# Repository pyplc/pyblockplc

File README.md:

# Python PLC Automation FBD- Programming with ESP32 Micropython

Pyblockplc is FBD programming for PLC, as PLC is here to be more precise an ESP32 uses Lolin D32 Pro.
Basis Micropython and as a PLC operating system a Python program called The ESP32 runs as
plc_os_v1_0.mpy, the program plc_os_v1_0.mpy is the main program in Mircopython is called in main.py in ESP32.
Pyblockplc IDE compiles a file called program.json, the file program.json must be loaded into the root directory of the ESP32 and restarted by restart or start the board.

pyblockplc FBD- Editor

pyblockplc Simulator

plc prototype hardware 24V, 6 input, 4 relais output.

Din rail case - APRA HO6

License:

PC program  pyblockplc _v1_0.exe - Freeware

Plc program plc_os_v1_0.mpy - Freeware

Hardware Kicad project - Licensed under CERN OHL v.1.2

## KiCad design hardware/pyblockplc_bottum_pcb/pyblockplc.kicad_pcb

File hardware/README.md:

# Prototyp PCB plc

Created with  KiCad 5.1.10

Licensed under CERN OHL v.1.2

PCB bottom:

PCB midle:

PCB top:

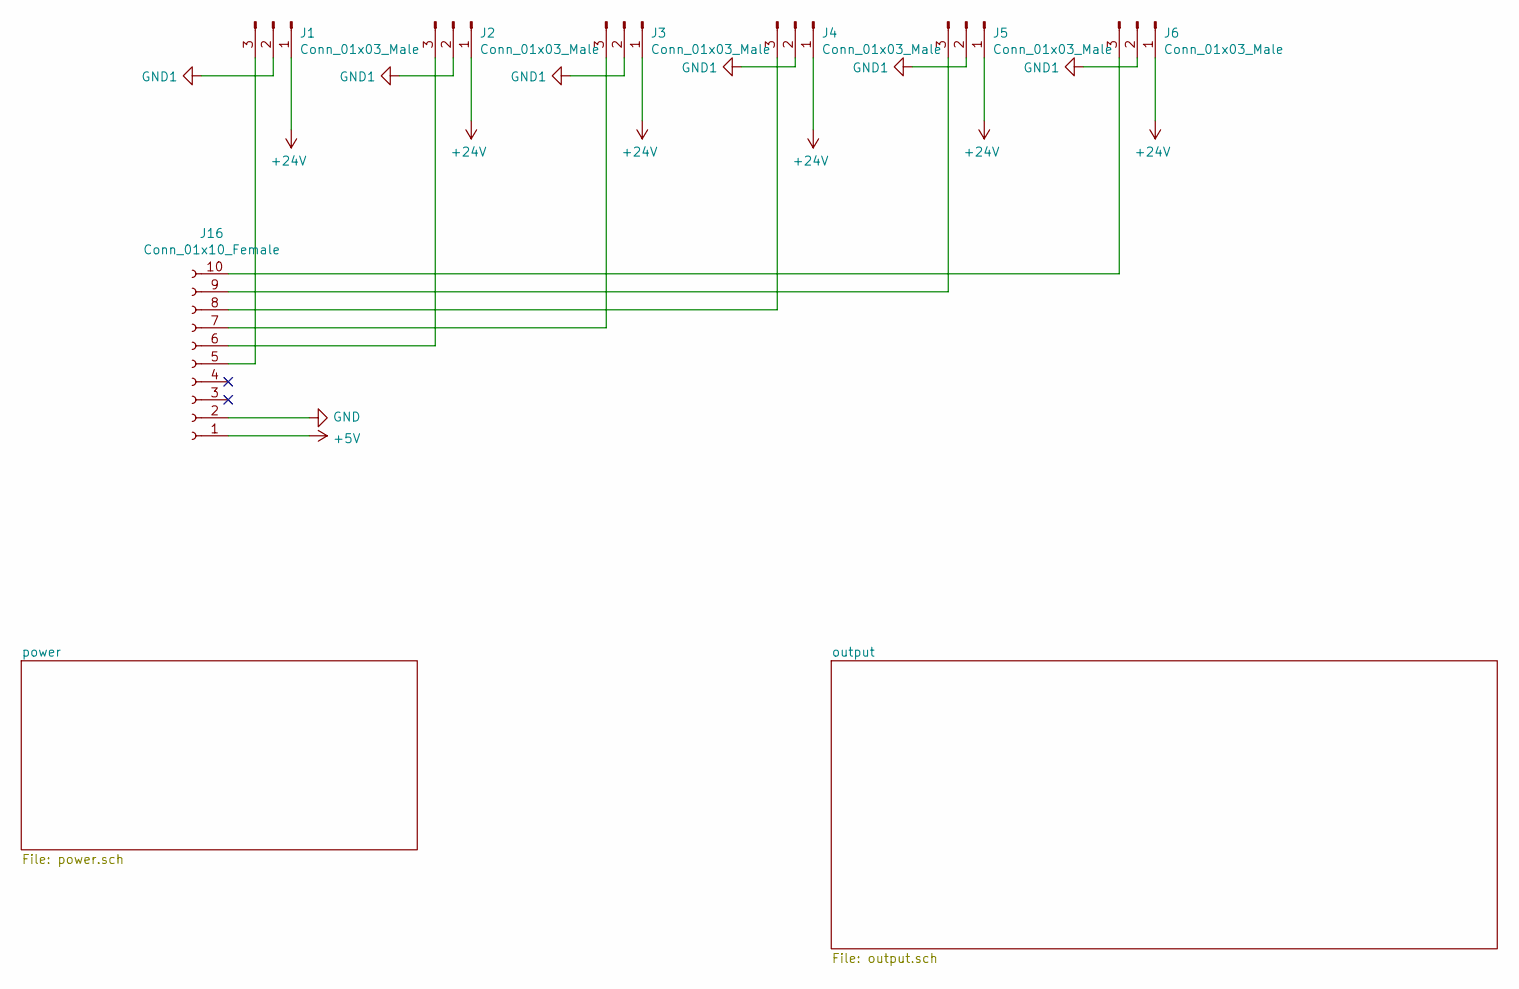
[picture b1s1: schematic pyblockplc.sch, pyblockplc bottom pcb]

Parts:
J1, J2, J3, J4, J5, J6: Conn_01x03_Male; JST_NV_B03P-NV_1x03_P5.00mm_Vertical
J16: Conn_01x10_Female; PinSocket_1x10_P2.54mm_Vertical

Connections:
+5V: J16.1; also elsewhere on the board
+24V: J1.1, J2.1, J3.1, J4.1, J5.1, J6.1; also elsewhere on the board
GND: J16.2; also elsewhere on the board
GND1: J1.2, J2.2, J3.2, J4.2, J5.2, J6.2; also elsewhere on the board
unnamed: J1.3, J16.5
unnamed: J2.3, J16.6
unnamed: J3.3, J16.7
unnamed: J4.3, J16.8
unnamed: J5.3, J16.9
unnamed: J6.3, J16.10

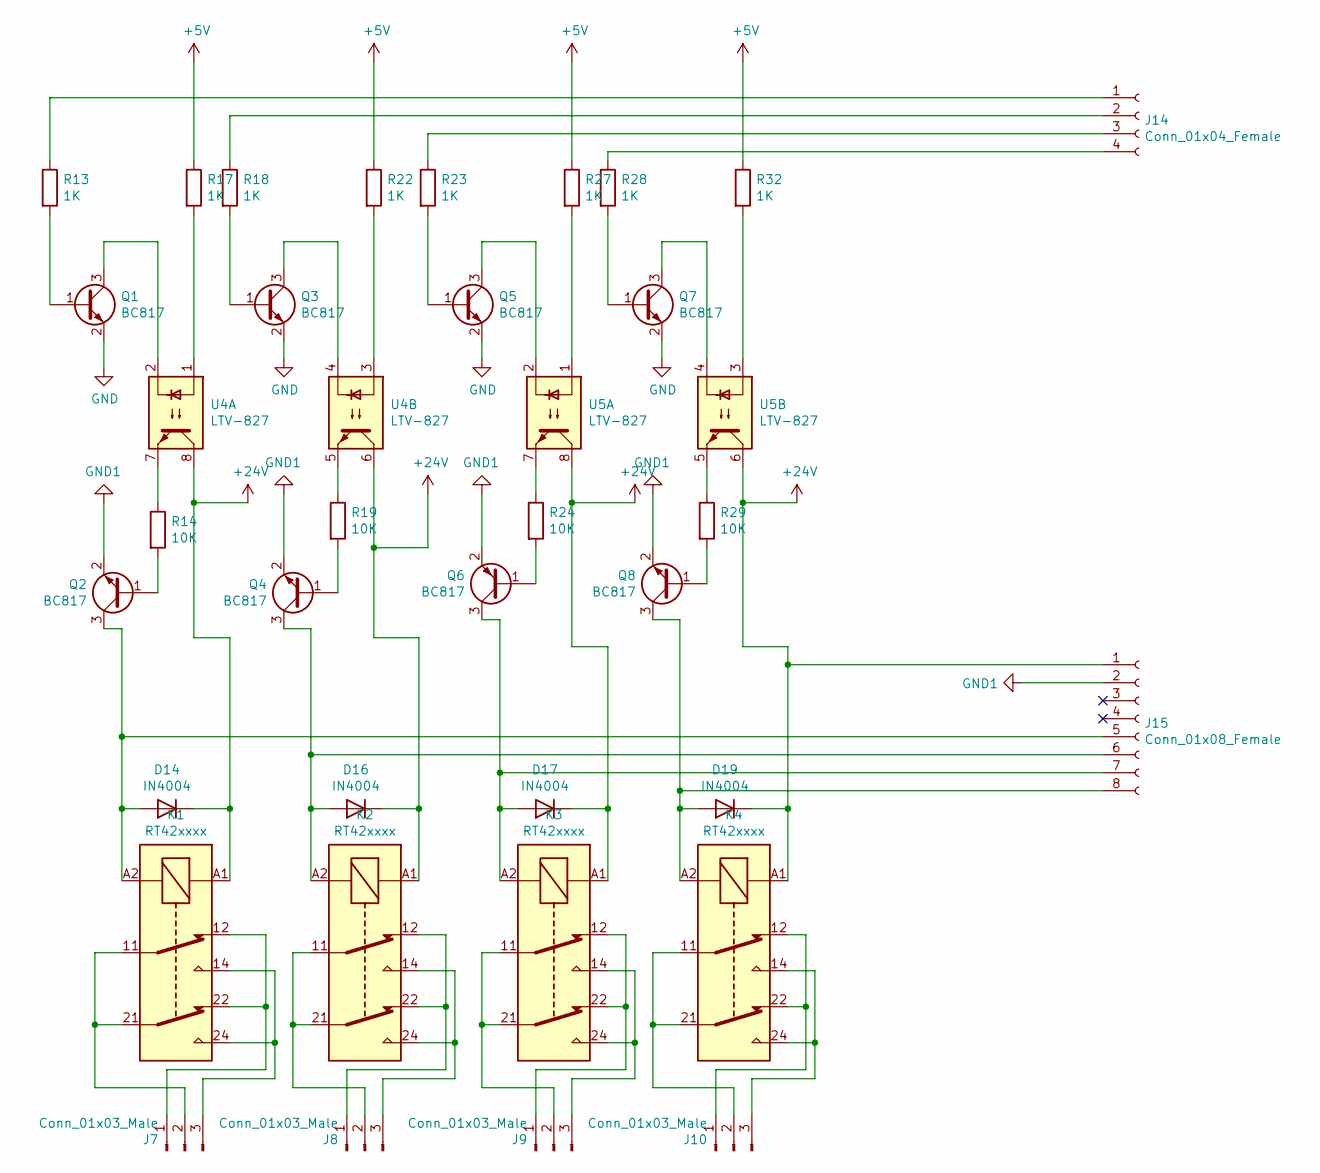
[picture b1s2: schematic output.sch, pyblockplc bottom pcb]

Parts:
D14, D16, D17, D19: IN4004; D_SMA
J7, J8, J9, J10: Conn_01x03_Male; JST_NV_B03P-NV_1x03_P5.00mm_Vertical
J14: Conn_01x04_Female; PinSocket_1x04_P2.54mm_Vertical
J15: Conn_01x08_Female; PinSocket_1x08_P2.54mm_Vertical
K1, K2, K3, K4: RT42xxxx; Relay_SPDT_Schrack-RP-II-1-16A-FormC_RM5mm
Q1, Q2, Q3, Q4, Q5, Q6, Q7, Q8: BC817; SOT-23
R13, R17, R18, R22, R23, R27, R28, R32: 1K; R_1206_3216Metric
R14, R19, R24, R29: 10K; R_1206_3216Metric
U4, U5: LTV-827; DIP-8_W8.89mm_SMDSocket_LongPads

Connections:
+5V: R17.1, R22.1, R27.1, R32.1; also elsewhere on the board
+24V: D14.1 (K), D16.1 (K), D17.1 (K), D19.1 (K), J15.1, K1.A1, K2.A1, K3.A1, K4.A1, U4.6, U4.8, U5.6, U5.8; also elsewhere on the board
GND: Q1.2 (E), Q3.2 (E), Q5.2 (E), Q7.2 (E); also elsewhere on the board
GND1: J15.2, Q2.2 (E), Q4.2 (E), Q6.2 (E), Q8.2 (E); also elsewhere on the board
unnamed: D14.2 (A), J15.5, K1.A2, Q2.3 (C)
unnamed: D16.2 (A), J15.6, K2.A2, Q4.3 (C)
unnamed: D17.2 (A), J15.7, K3.A2, Q6.3 (C)
unnamed: D19.2 (A), J15.8, K4.A2, Q8.3 (C)
unnamed: J7.1, K1.12, K1.22
unnamed: J7.2, K1.11, K1.21
unnamed: J7.3, K1.14, K1.24
unnamed: J8.1, K2.12, K2.22
unnamed: J8.2, K2.11, K2.21
unnamed: J8.3, K2.14, K2.24
unnamed: J9.1, K3.12, K3.22
unnamed: J9.2, K3.11, K3.21
unnamed: J9.3, K3.14, K3.24
unnamed: J10.1, K4.12, K4.22
unnamed: J10.2, K4.11, K4.21
unnamed: J10.3, K4.14, K4.24
unnamed: J14.1, R13.1
unnamed: J14.2, R18.1
unnamed: J14.3, R23.1
unnamed: J14.4, R28.1
unnamed: Q1.1 (B), R13.2
unnamed: Q1.3 (C), U4.2
unnamed: Q2.1 (B), R14.2
unnamed: Q3.1 (B), R18.2
unnamed: Q3.3 (C), U4.4
unnamed: Q4.1 (B), R19.2
unnamed: Q5.1 (B), R23.2
unnamed: Q5.3 (C), U5.2
unnamed: Q6.1 (B), R24.2
unnamed: Q7.1 (B), R28.2
unnamed: Q7.3 (C), U5.4
unnamed: Q8.1 (B), R29.2
unnamed: R14.1, U4.7
unnamed: R17.2, U4.1
unnamed: R19.1, U4.5
unnamed: R22.2, U4.3
unnamed: R24.1, U5.7
unnamed: R27.2, U5.1
unnamed: R29.1, U5.5
unnamed: R32.2, U5.3

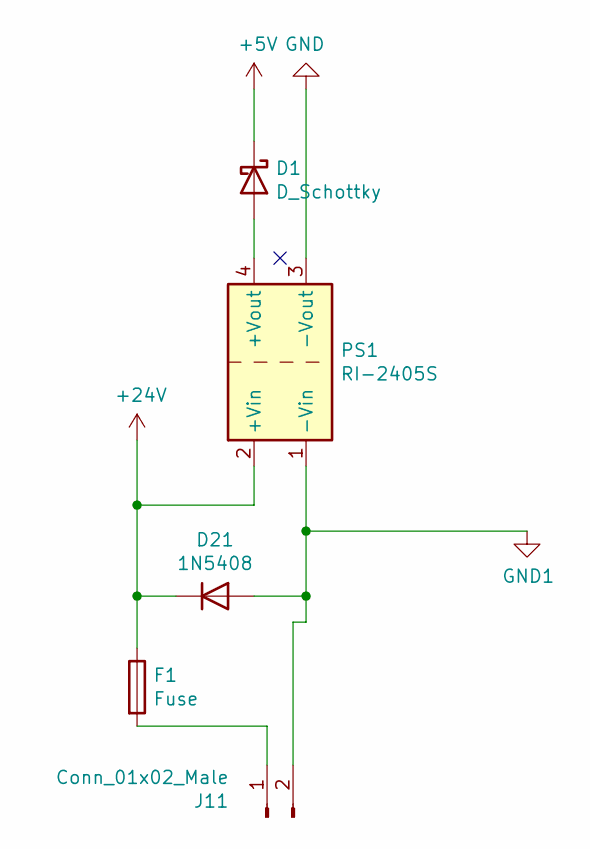
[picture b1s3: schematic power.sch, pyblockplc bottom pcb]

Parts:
D1: D_Schottky; D_SMA
D21: 1N5408; D_DO-201AD_P15.24mm_Horizontal
F1: Fuse; Fuseholder_Cylinder-5x20mm_Schurter_0031_8201_Horizontal_Op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
J11: Conn_01x02_Male; JST_NV_B02P-NV_1x02_P5.00mm_Vertical
PS1: RI-2405S; Converter_DCDC_RECOM_R-78S-0.1_THT

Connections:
+5V: D1.1 (K); also elsewhere on the board
+24V: D21.1 (K), F1.1, PS1.2 (+Vin); also elsewhere on the board
GND: PS1.3 (-Vout); also elsewhere on the board
GND1: D21.2 (A), J11.2, PS1.1 (-Vin); also elsewhere on the board
unnamed: D1.2 (A), PS1.4 (+Vout)
unnamed: F1.2, J11.1

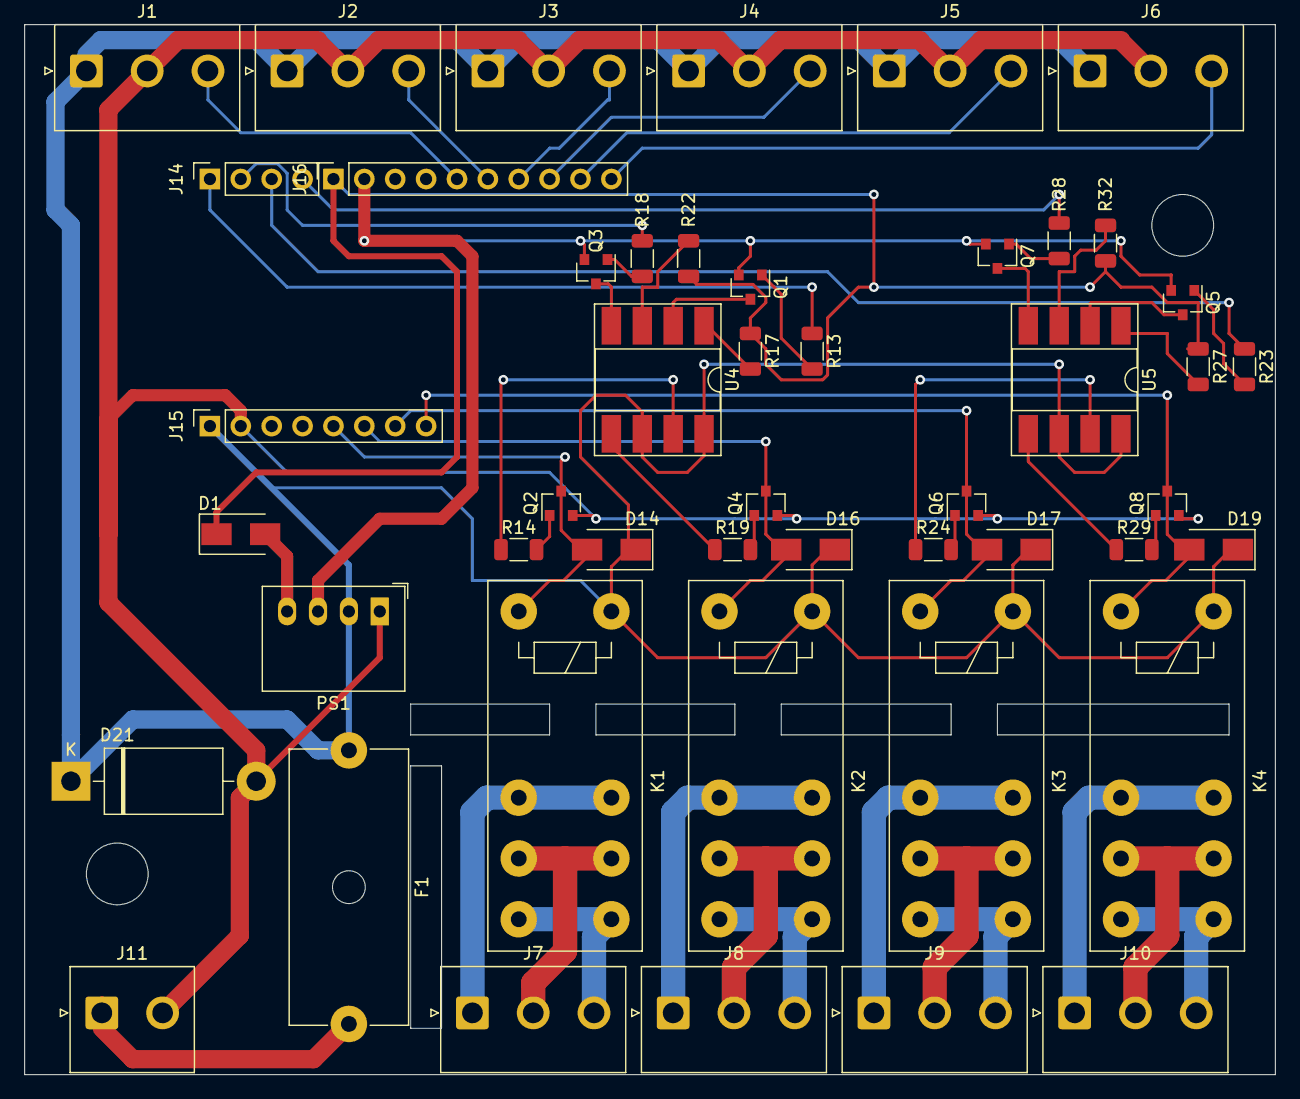
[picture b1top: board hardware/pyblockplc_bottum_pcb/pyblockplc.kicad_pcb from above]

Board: 2 copper layers, 102.9 x 86.4 mm, 48 parts (0 on the bottom side), 52 nets.

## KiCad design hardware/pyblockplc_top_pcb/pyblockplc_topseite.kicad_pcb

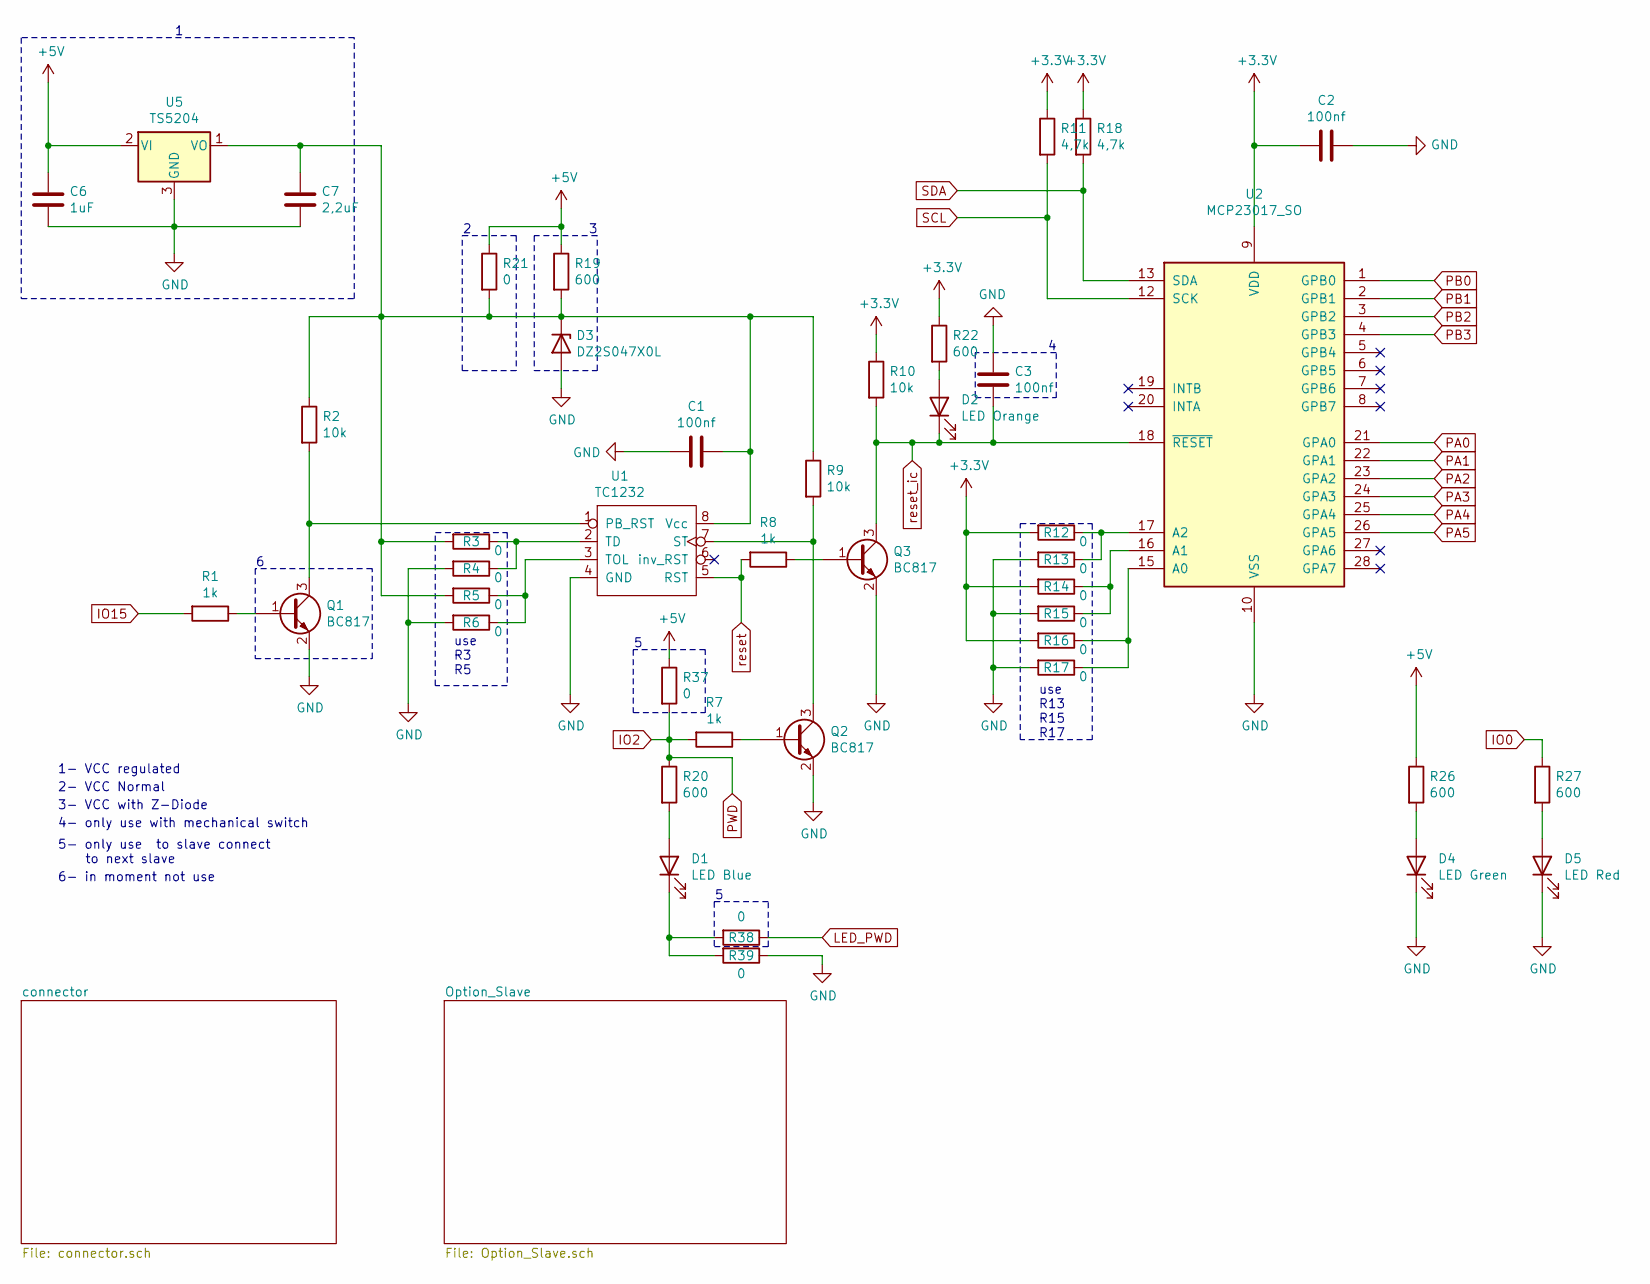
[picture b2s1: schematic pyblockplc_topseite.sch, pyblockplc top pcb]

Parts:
C1, C2, C3: 100nf; C_1206_3216Metric
C6: 1uF; CP_Elec_4x5.8
C7: 2,2uF; CP_Elec_4x5.8
D1: LED Blue; LED_1206_3216Metric_Castellated
D2: LED Orange; LED_1206_3216Metric_Castellated
D3: DZ2S047X0L; D_1206_3216Metric
D4: LED Green; LED_1206_3216Metric_Castellated
D5: LED Red; LED_1206_3216Metric_Castellated
Q1, Q2, Q3: BC817; SOT-23
R1, R7, R8: 1k; R_1206_3216Metric
R2, R9, R10: 10k; R_1206_3216Metric
R3, R4, R5, R6, R12, R13, R14, R15, R16, R17, R21, R37, R38, R39: 0; R_1206_3216Metric
R11, R18: 4,7k; R_1206_3216Metric
R19, R20, R22, R26, R27: 600; R_1206_3216Metric
U1: TC1232; SOIC-8_3.9x4.9mm_P1.27mm
U2: MCP23017_SO; SOIC-28W_7.5x17.9mm_P1.27mm
U5: TS5204; SOT-23

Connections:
+3V3: C2.2, R10.1, R11.1, R12.2, R14.2, R16.2, R18.1, R22.1, U2.9 (VDD); also elsewhere on the board
+5V: C6.1, R19.1, R21.1, R26.1, R37.1, U5.2 (VI); also elsewhere on the board
GND: C1.2, C2.1, C3.1, C6.2, C7.2, D3.2 (A), D4.1 (K), D5.1 (K), Q1.2 (E), Q2.2 (E), Q3.2 (E), R4.2, R6.2, R13.2, R15.2, R17.2, R39.1, U1.4 (GND), U2.10 (VSS), U5.3 (GND); also elsewhere on the board
IO0: R27.1; also elsewhere on the board
IO2: R7.2, R20.1, R37.2; also elsewhere on the board
IO15: R1.2; also elsewhere on the board
LED_PWD: R38.1; also elsewhere on the board
unnamed: C1.1, C7.1, D3.1 (K), R2.1, R3.2, R5.2, R9.1, R19.2, R21.2, U1.8 (Vcc), U5.1 (VO)
unnamed: D1.1 (K), R38.2, R39.2
unnamed: D1.2 (A), R20.2
unnamed: D2.2 (A), R22.2
unnamed: D4.2 (A), R26.2
unnamed: D5.2 (A), R27.2
unnamed: Q1.1 (B), R1.1
unnamed: Q1.3 (C), R2.2, U1.1 (PB_RST)
unnamed: Q2.1 (B), R7.1
unnamed: Q2.3 (C), R9.2, U1.7 (ST)
unnamed: Q3.1 (B), R8.1
unnamed: R3.1, R4.1, U1.2 (TD)
unnamed: R5.1, R6.1, U1.3 (TOL)
unnamed: R12.1, R13.1, U2.17 (A2)
unnamed: R14.1, R15.1, U2.16 (A1)
unnamed: R16.1, R17.1, U2.15 (A0)
PA0: U2.21 (GPA0); also elsewhere on the board
PA1: U2.22 (GPA1); also elsewhere on the board
PA2: U2.23 (GPA2); also elsewhere on the board
PA3: U2.24 (GPA3); also elsewhere on the board
PA4: U2.25 (GPA4); also elsewhere on the board
PA5: U2.26 (GPA5); also elsewhere on the board
PB0: U2.1 (GPB0); also elsewhere on the board
PB1: U2.2 (GPB1); also elsewhere on the board
PB2: U2.3 (GPB2); also elsewhere on the board
PB3: U2.4 (GPB3); also elsewhere on the board
SCL: R11.2, U2.12 (SCK); also elsewhere on the board
SDA: R18.2, U2.13 (SDA); also elsewhere on the board
reset: R8.2, U1.5 (RST); also elsewhere on the board
reset_ic: C3.2, D2.1 (K), Q3.3 (C), R10.2, U2.18 (~RESET~); also elsewhere on the board

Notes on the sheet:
2- VCC Normal
3- VCC with Z-Diode
1- VCC regulated
4- only use with mechanical switch
5- only use to slave connect to next slave
use R3 R5
use R13 R15 R17
6- in moment not use

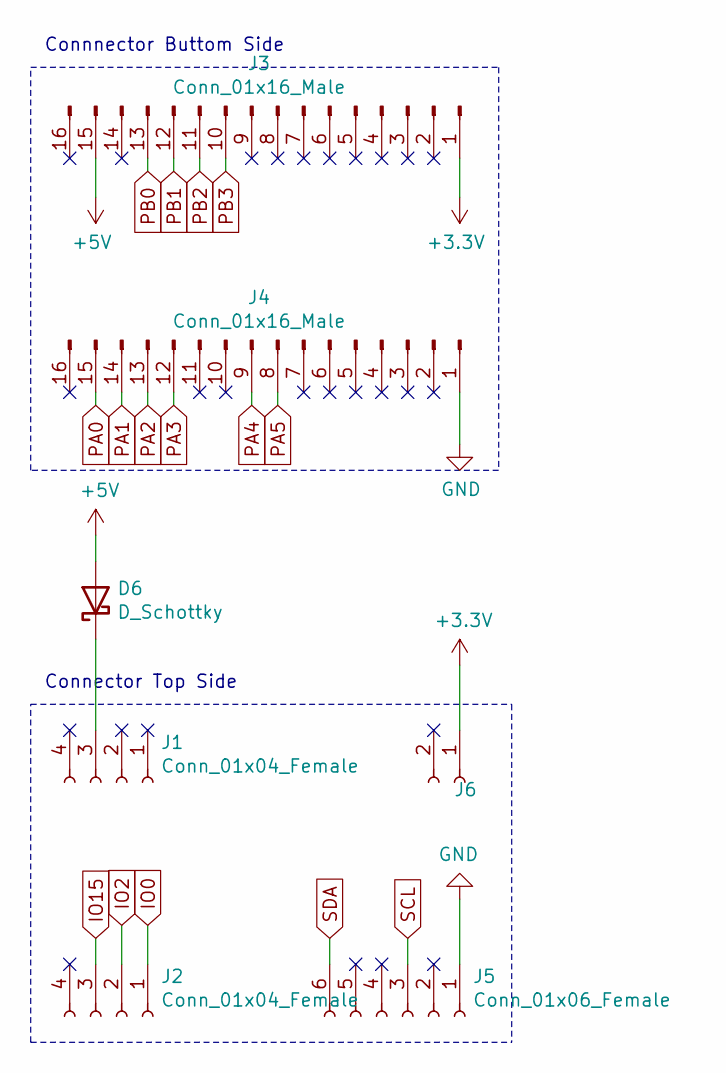
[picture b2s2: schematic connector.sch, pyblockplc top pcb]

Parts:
D6: D_Schottky; D_SMA
J1, J2: Conn_01x04_Female; PinSocket_1x04_P2.54mm_Vertical
J3, J4: Conn_01x16_Male; PinHeader_1x16_P2.54mm_Vertical
J5: Conn_01x06_Female; PinSocket_1x06_P2.54mm_Vertical
J6: Conn_01x02_Female; PinSocket_1x02_P2.54mm_Vertical

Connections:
+3V3: J3.1, J6.1; also elsewhere on the board
+5V: D6.2 (A), J3.15; also elsewhere on the board
GND: J4.1, J5.1; also elsewhere on the board
IO0: J2.1; also elsewhere on the board
IO2: J2.2; also elsewhere on the board
IO15: J2.3; also elsewhere on the board
unnamed: D6.1 (K), J1.3
PA0: J4.15; also elsewhere on the board
PA1: J4.14; also elsewhere on the board
PA2: J4.13; also elsewhere on the board
PA3: J4.12; also elsewhere on the board
PA4: J4.9; also elsewhere on the board
PA5: J4.8; also elsewhere on the board
PB0: J3.13; also elsewhere on the board
PB1: J3.12; also elsewhere on the board
PB2: J3.11; also elsewhere on the board
PB3: J3.10; also elsewhere on the board
SCL: J5.3; also elsewhere on the board
SDA: J5.6; also elsewhere on the board

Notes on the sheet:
Connnector Buttom Side
Connector Top Side

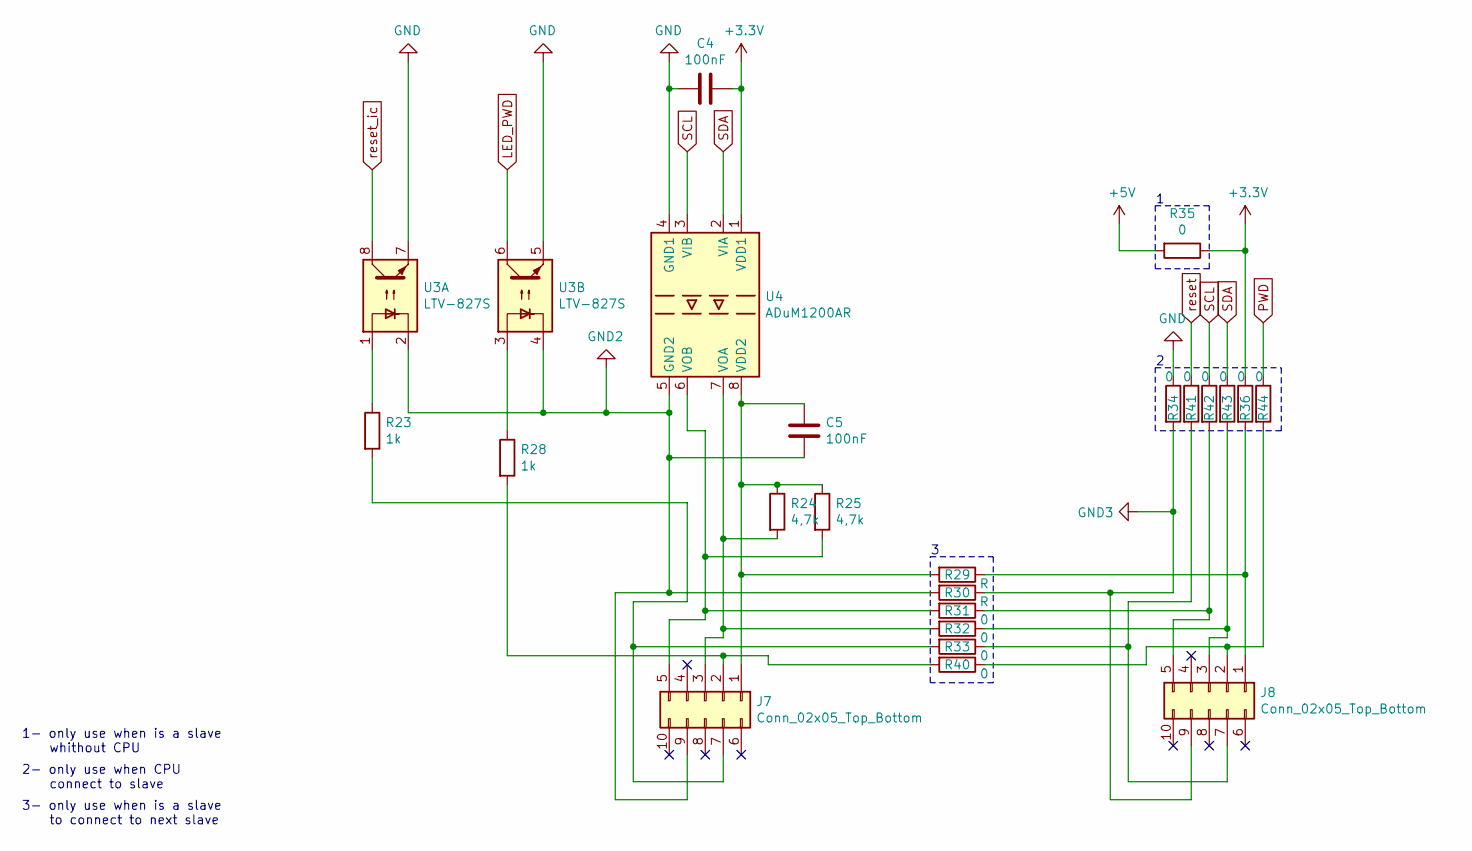
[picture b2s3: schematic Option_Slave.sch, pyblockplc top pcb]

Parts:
C4, C5: 100nF; C_1206_3216Metric
J7, J8: Conn_02x05_Top_Bottom; PinHeader_2x05_P2.54mm_Vertical
R23, R28: 1k; R_1206_3216Metric
R24, R25: 4,7k; R_1206_3216Metric
R29, R30: R; R_1206_3216Metric
R31, R32, R33, R34, R35, R36, R40, R41, R42, R43, R44: 0; R_1206_3216Metric
U3: LTV-827S; SMDIP-8_W9.53mm
U4: ADuM1200AR; SOIC-8_3.9x4.9mm_P1.27mm

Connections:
+3V3: C4.1, R35.1, R36.1, U4.1 (VDD1); also elsewhere on the board
+5V: R35.2; also elsewhere on the board
GND: C4.2, R34.1, U3.5, U3.7, U4.4 (GND1); also elsewhere on the board
GND2: C5.2, J7.9, R30.2, U3.2, U3.4, U4.5 (GND2)
GND3: J8.9, R30.1, R34.2
IO2: R44.1; also elsewhere on the board
LED_PWD: U3.6; also elsewhere on the board
unnamed: C5.1, J7.1, R24.1, R25.1, R29.2, U4.8 (VDD2)
unnamed: J7.2, R28.2, R40.2
unnamed: J7.3, R24.2, R32.2, U4.7 (VOA)
unnamed: J7.5, R25.2, R31.2, U4.6 (VOB)
unnamed: J7.7, R23.2, R33.2
unnamed: J8.1, R29.1, R36.2
unnamed: J8.2, R40.1, R44.2
unnamed: J8.3, R32.1, R43.2
unnamed: J8.5, R31.1, R42.2
unnamed: J8.7, R33.1, R41.2
unnamed: R23.1, U3.1
unnamed: R28.1, U3.3
SCL: R42.1, U4.3 (VIB); also elsewhere on the board
SDA: R43.1, U4.2 (VIA); also elsewhere on the board
reset: R41.1; also elsewhere on the board
reset_ic: U3.8; also elsewhere on the board

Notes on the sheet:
1- only use when is a slave whithout CPU
2- only use when CPU connect to slave
3- only use when is a slave to connect to next slave

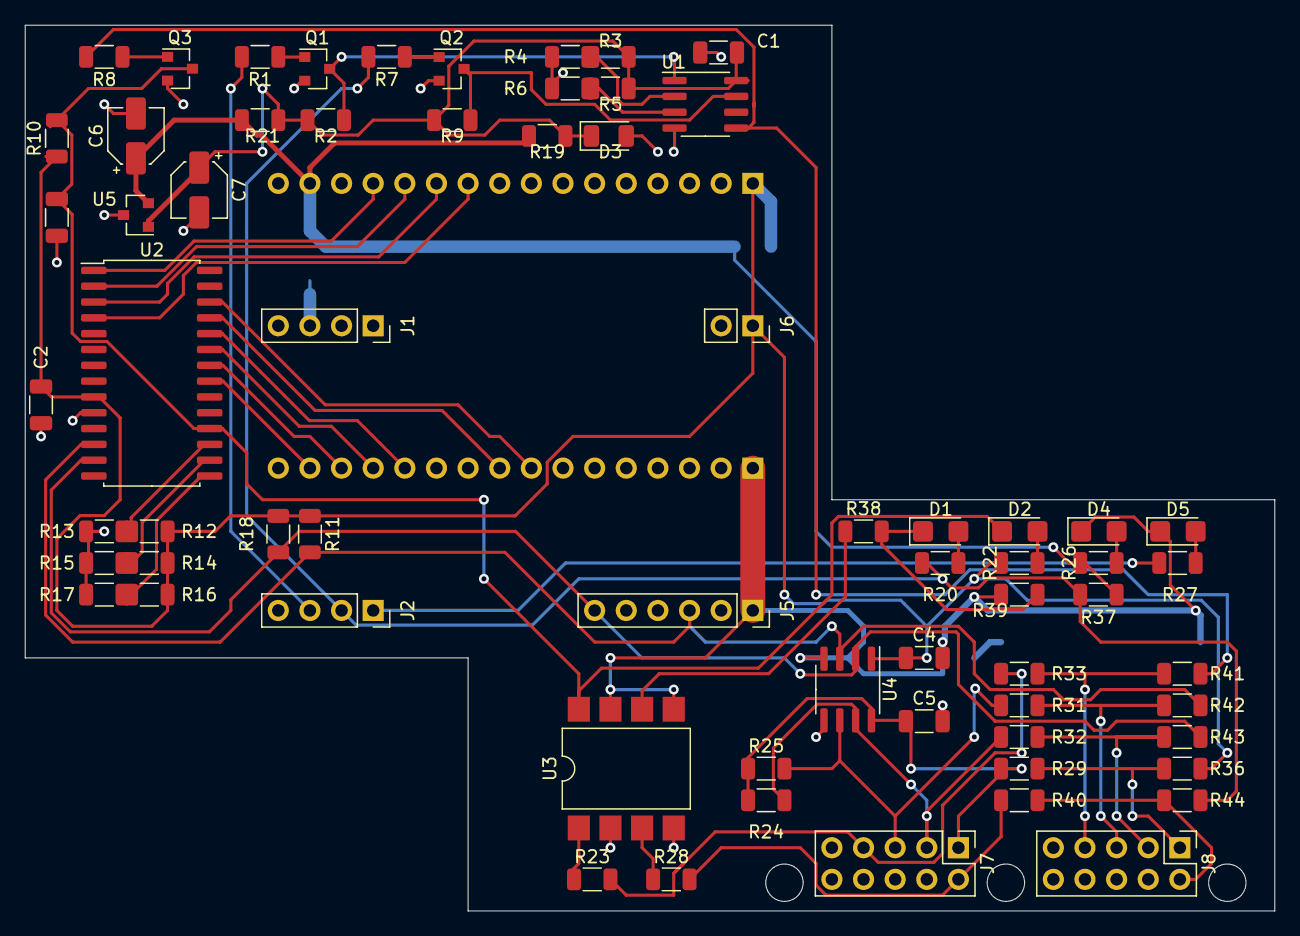
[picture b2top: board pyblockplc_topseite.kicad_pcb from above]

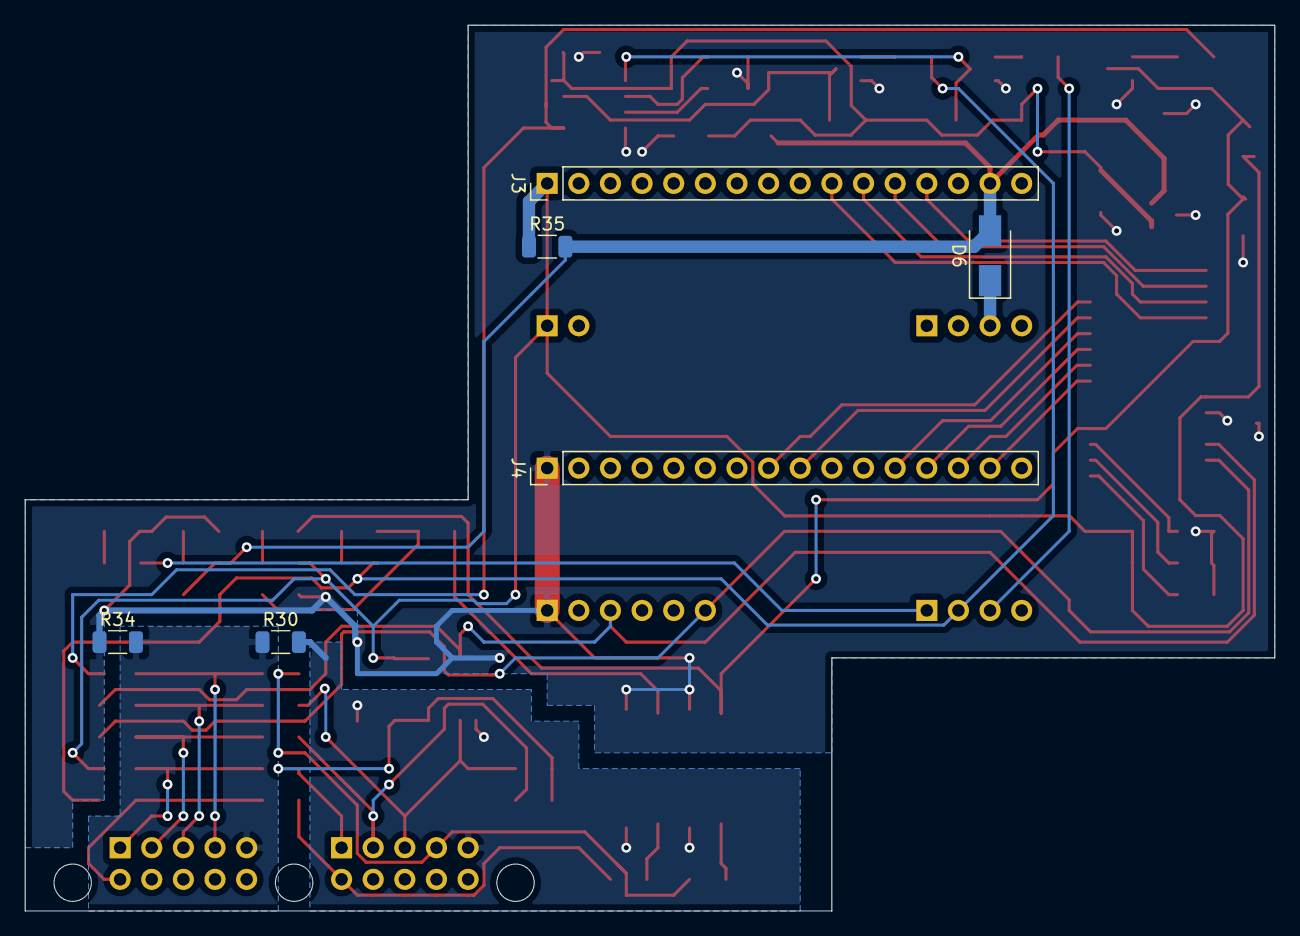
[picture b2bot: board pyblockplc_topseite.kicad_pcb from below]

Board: 2 copper layers, 100.3 x 71.1 mm, 73 parts (6 on the bottom side), 52 nets.

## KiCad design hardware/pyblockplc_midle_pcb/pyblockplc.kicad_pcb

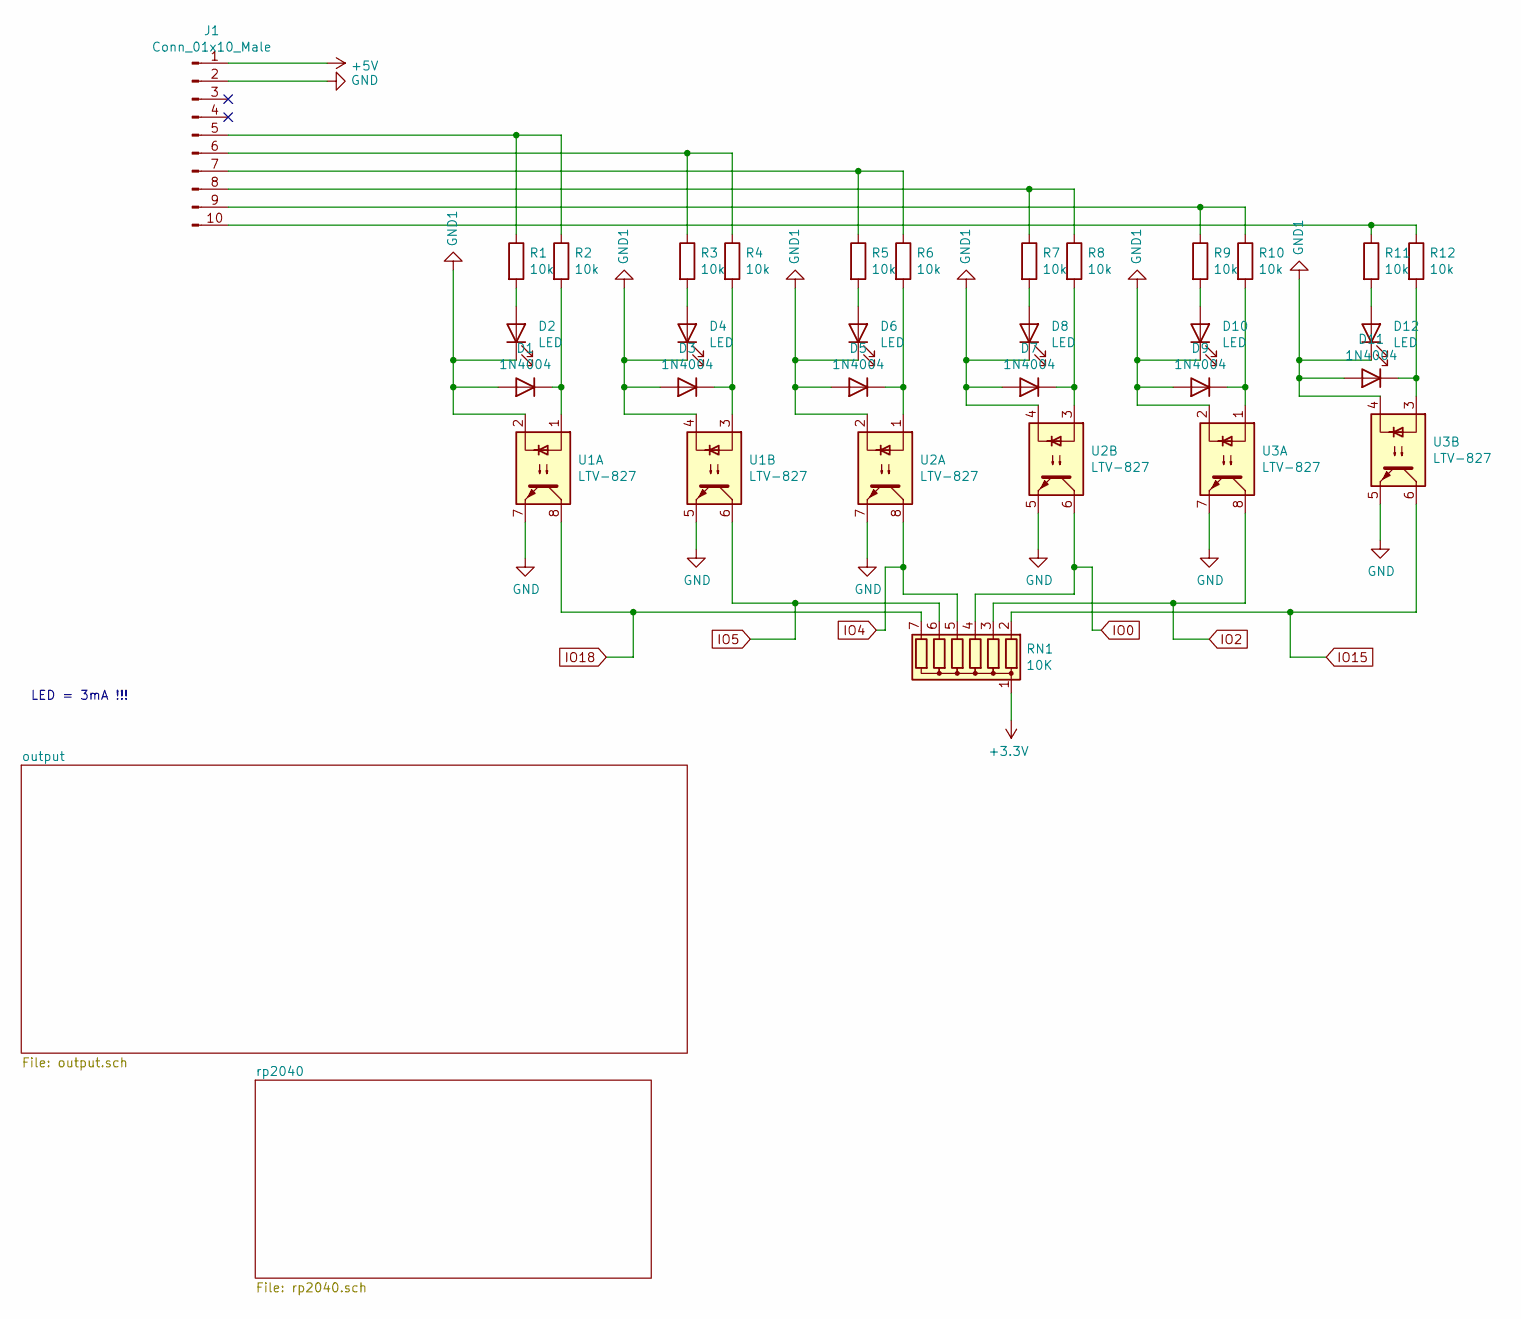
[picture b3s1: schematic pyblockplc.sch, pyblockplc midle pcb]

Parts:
D1, D3, D5, D7, D9, D11: 1N4004; D_SMA
D2, D4, D6, D8, D10, D12: LED; LED_D3.0mm
J1: Conn_01x10_Male; PinHeader_1x10_P2.54mm_Vertical
R1, R2, R3, R4, R5, R6, R7, R8, R9, R10, R11, R12: 10k; R_1206_3216Metric
RN1: 10K; R_Array_SIP7
U1, U2, U3: LTV-827; DIP-8_W8.89mm_SMDSocket_LongPads

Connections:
+3V3: RN1.1 (common); also elsewhere on the board
+5V: J1.1; also elsewhere on the board
GND: J1.2, U1.5, U1.7, U2.5, U2.7, U3.5, U3.7; also elsewhere on the board
GND1: D1.2 (A), D2.1 (K), D3.2 (A), D4.1 (K), D5.2 (A), D6.1 (K), D7.2 (A), D8.1 (K), D9.2 (A), D10.1 (K), D11.2 (A), D12.1 (K), U1.2, U1.4, U2.2, U2.4, U3.2, U3.4; also elsewhere on the board
IO0: RN1.4 (R3), U2.6; also elsewhere on the board
IO2: RN1.3 (R2), U3.8; also elsewhere on the board
IO4: RN1.5 (R4), U2.8; also elsewhere on the board
IO5: RN1.6 (R5), U1.6; also elsewhere on the board
IO15: RN1.2 (R1), U3.6; also elsewhere on the board
IO18: RN1.7 (R6), U1.8; also elsewhere on the board
unnamed: D1.1 (K), R2.2, U1.1
unnamed: D2.2 (A), R1.2
unnamed: D3.1 (K), R4.2, U1.3
unnamed: D4.2 (A), R3.2
unnamed: D5.1 (K), R6.2, U2.1
unnamed: D6.2 (A), R5.2
unnamed: D7.1 (K), R8.2, U2.3
unnamed: D8.2 (A), R7.2
unnamed: D9.1 (K), R10.2, U3.1
unnamed: D10.2 (A), R9.2
unnamed: D11.1 (K), R12.2, U3.3
unnamed: D12.2 (A), R11.2
unnamed: J1.5, R1.1, R2.1
unnamed: J1.6, R3.1, R4.1
unnamed: J1.7, R5.1, R6.1
unnamed: J1.8, R7.1, R8.1
unnamed: J1.9, R9.1, R10.1
unnamed: J1.10, R11.1, R12.1

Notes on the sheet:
LED = 3mA !!!

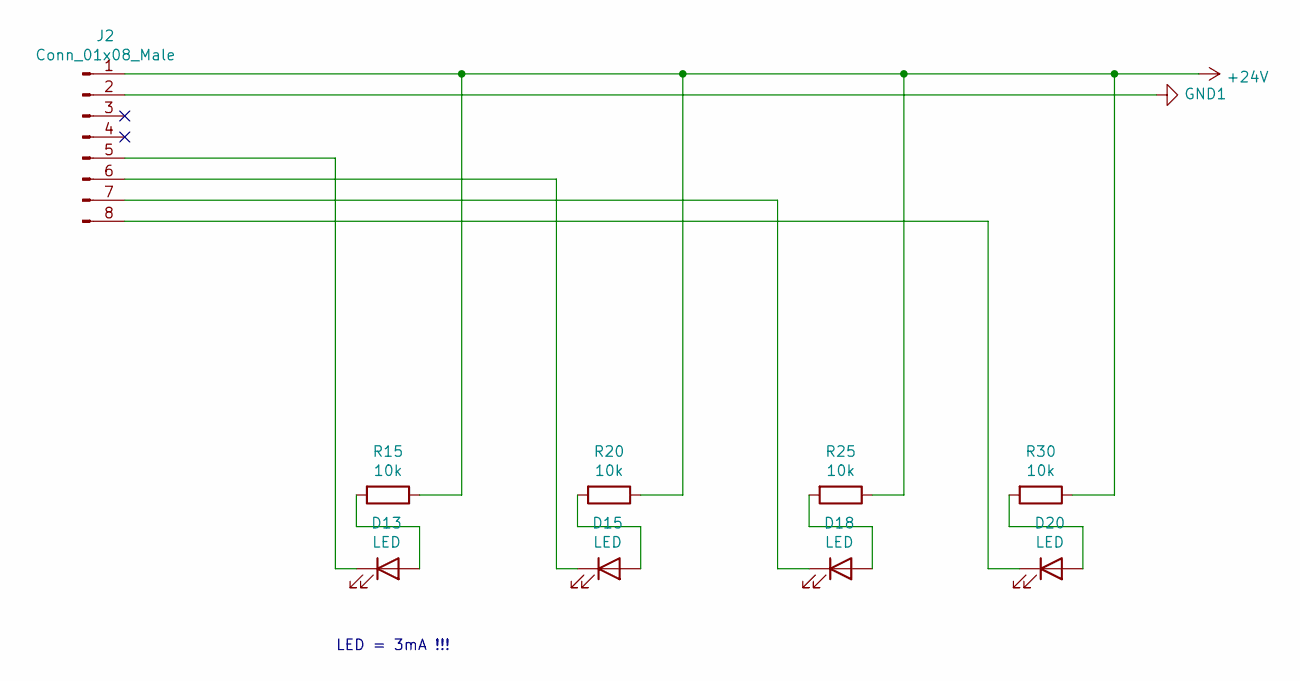
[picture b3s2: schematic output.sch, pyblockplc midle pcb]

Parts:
D13, D15, D18, D20: LED; LED_D3.0mm
J2: Conn_01x08_Male; PinHeader_1x08_P2.54mm_Vertical
R15, R20, R25, R30: 10k; R_1206_3216Metric

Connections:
+24V: J2.1, R15.1, R20.1, R25.1, R30.1
GND1: J2.2; also elsewhere on the board
unnamed: D13.1 (K), J2.5
unnamed: D13.2 (A), R15.2
unnamed: D15.1 (K), J2.6
unnamed: D15.2 (A), R20.2
unnamed: D18.1 (K), J2.7
unnamed: D18.2 (A), R25.2
unnamed: D20.1 (K), J2.8
unnamed: D20.2 (A), R30.2

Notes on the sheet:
LED = 3mA !!!

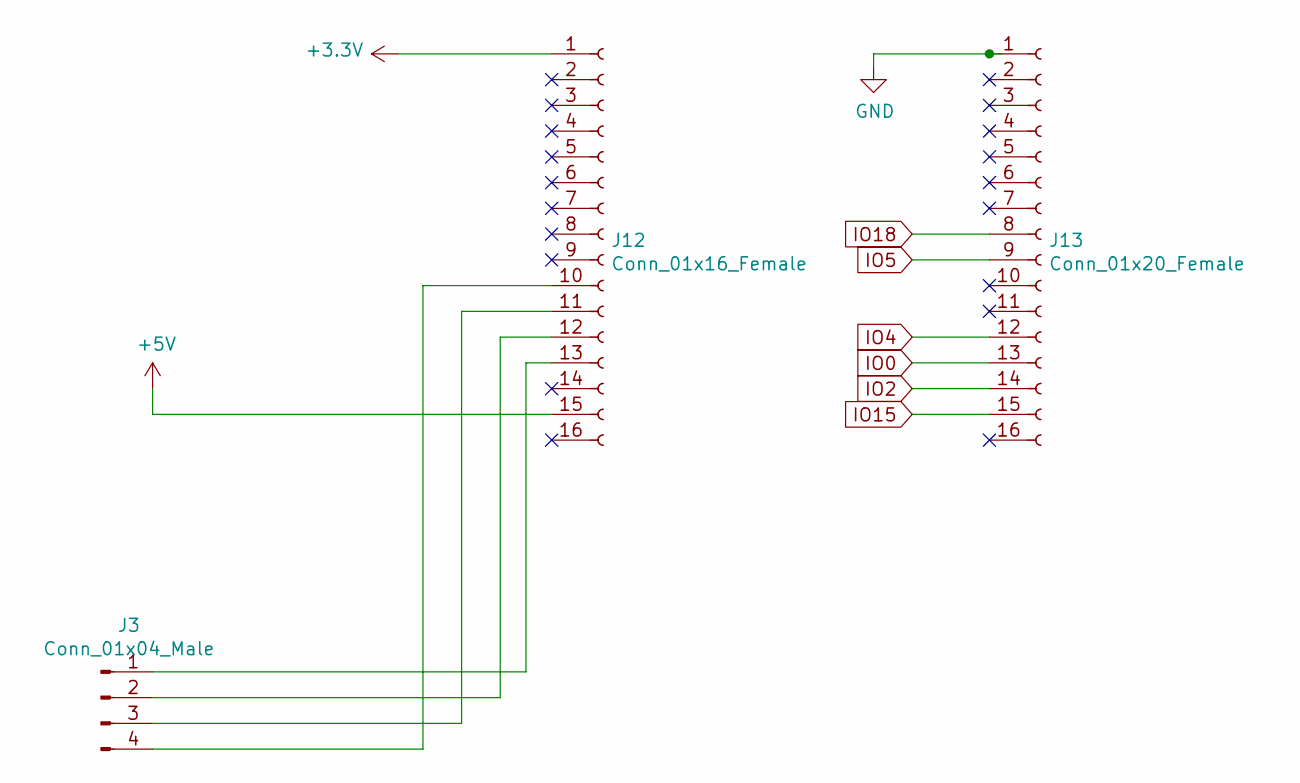
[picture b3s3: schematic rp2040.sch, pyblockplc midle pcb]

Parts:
J3: Conn_01x04_Male; PinHeader_1x04_P2.54mm_Vertical
J12: Conn_01x16_Female; PinSocket_1x16_P2.54mm_Vertical
J13: Conn_01x20_Female; PinSocket_1x16_P2.54mm_Vertical

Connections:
+3V3: J12.1; also elsewhere on the board
+5V: J12.15; also elsewhere on the board
GND: J13.1; also elsewhere on the board
IO0: J13.13; also elsewhere on the board
IO2: J13.14; also elsewhere on the board
IO4: J13.12; also elsewhere on the board
IO5: J13.9; also elsewhere on the board
IO15: J13.15; also elsewhere on the board
IO18: J13.8; also elsewhere on the board
unnamed: J3.4, J12.10
unnamed: J3.3, J12.11
unnamed: J3.2, J12.12
unnamed: J3.1, J12.13
